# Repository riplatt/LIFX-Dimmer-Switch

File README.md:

# LIFX-Dimmer-Switch
A Dimmer switch for the LIFX lights

Control the LIFX light with a physical dimmer switch

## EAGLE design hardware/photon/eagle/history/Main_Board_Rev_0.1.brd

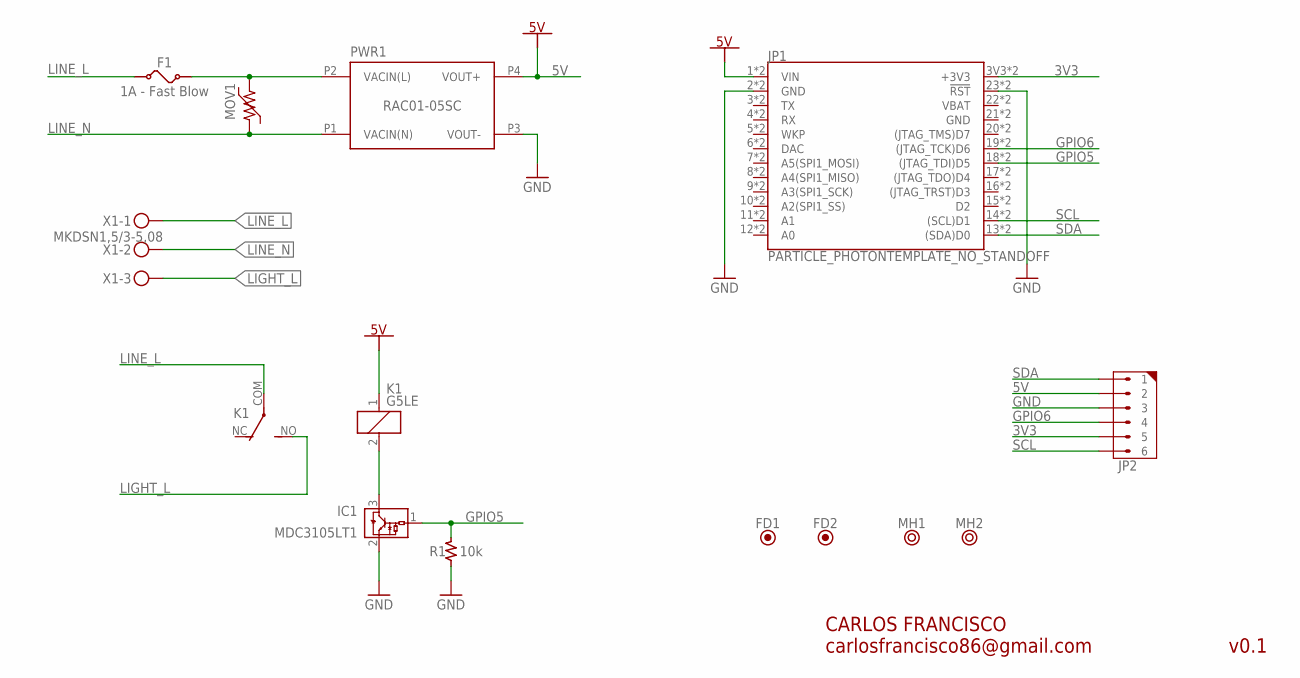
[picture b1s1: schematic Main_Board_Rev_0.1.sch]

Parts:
F1: 1A - Fast Blow; FUSE3.6X10MM
FD1, FD2: FIDUCIALBFID; BOARD_FIDUCIAL
IC1: MDC3105LT1; SOT23
JP1: PARTICLE_PHOTONTEMPLATE_NO_STANDOFF; PARTICLE_PHOTON_TEMPLATE_NO_STANDOFF
JP2: 6X1THT_254MM; HDRV6W63P254_6X1_1520X280H680
K1: G5LE
MH1, MH2: MOUNTING_HOLE3.5MM; MTGP500H350
MOV1: MOV-ROV10H_P; ROV10H_P
PWR1: RAC01-05SC; LOW_PROFILE_POWER_MODULE
R1: 10k; RESC2012X60L35N
X1: MKDSN1,5/3-5,08

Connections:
3V3: JP1.3V3 (+3V3), JP1.24 (+3V3), JP2.5
5V: JP1.1 (VIN), JP1.VIN, JP2.2, K1.1, PWR1.P4 (VOUT+)
GND: IC1.2 (GND), JP1.2 (GND), JP1.21 (GND), JP1.23 (!RST!), JP1.GND@0 (GND), JP1.GND@2 (GND), JP1.RST (!RST!), JP2.3, PWR1.P3 (VOUT-), R1.1
GPIO5: IC1.1 (VIN), JP1.18 ((JTAG_TDI)D5), JP1.D5 ((JTAG_TDI)D5), R1.2
GPIO6: JP1.19 ((JTAG_TCK)D6), JP1.D6 ((JTAG_TCK)D6), JP2.4
LIGHT_L: K1.NO (S), X1.3
LINE_L: F1.P$1, K1.COM, X1.1
LINE_L_F: F1.P$2, MOV1.2, PWR1.P2 (VACIN(L))
LINE_N: MOV1.1, PWR1.P1 (VACIN(N)), X1.2
unnamed: IC1.3 (VOUT), K1.2
SCL: JP1.14 ((SCL)D1), JP1.D1 ((SCL)D1), JP2.6
SDA: JP1.13 ((SDA)D0), JP1.D0 ((SDA)D0), JP2.1
VBAT: JP1.22 (VBAT), JP1.VBAT

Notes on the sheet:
CARLOS FRANCISCO carlosfrancisco86@gmail.com
v0.1

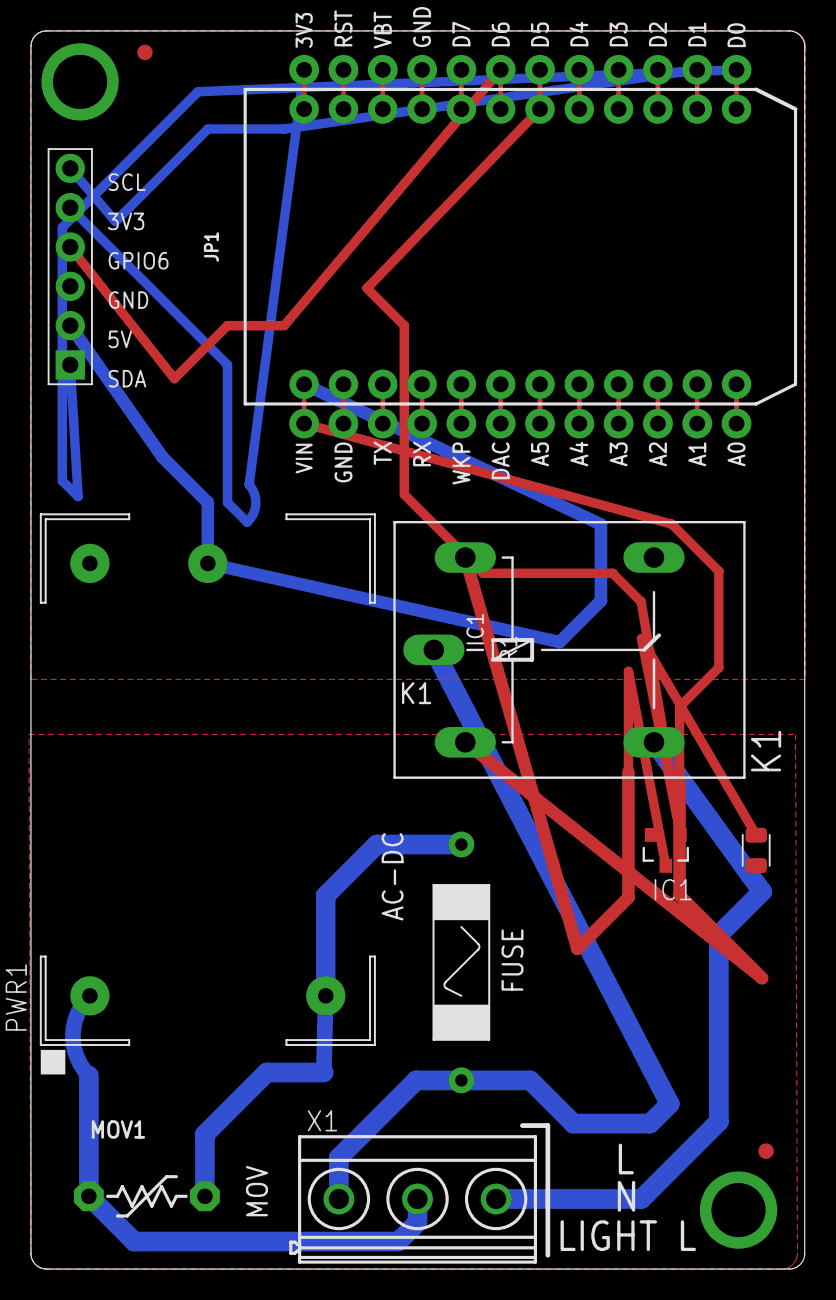
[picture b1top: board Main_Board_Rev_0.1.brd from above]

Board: 2 copper layers, 50.0 x 80.0 mm, 13 parts (0 on the bottom side), 13 nets.

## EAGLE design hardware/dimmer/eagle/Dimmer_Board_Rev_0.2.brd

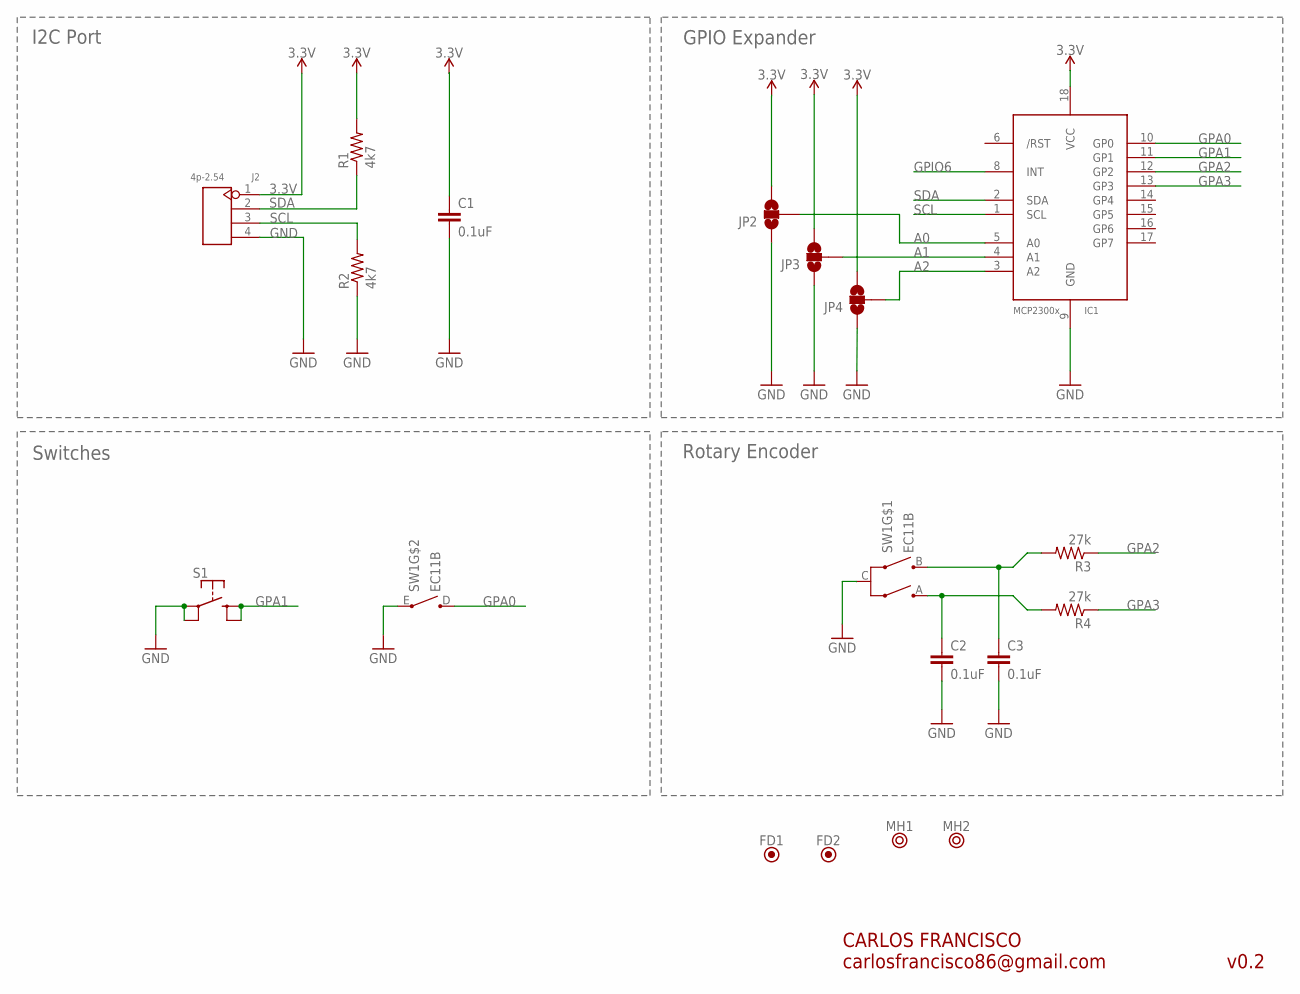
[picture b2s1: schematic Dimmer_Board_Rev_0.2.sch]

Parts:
C1, C2, C3: 0.1uF; C0805
FD1, FD2: FIDUCIALBFID; BOARD_FIDUCIAL
IC1: MCP23008/SO; SO18W
J2: 4p-2.54; H4-2.54
JP2, JP3, JP4: JUMPER-SMT_3_NO_SILK; SMT-JUMPER_3_NO_SILK
MH1, MH2: MOUNTING_HOLE3.5MM; MTGP500H350
R1, R2: 4k7; R0805
R3, R4: 27k; R0805
S1: BUTTON-4KSC; KSC_X
SW1: EC11B; EC11B-V

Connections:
3.3V: C1.1, IC1.18 (VCC), J2.1, JP2.3, JP3.3, JP4.3, R1.2
A: C2.1, R4.2, SW1.A
A0: IC1.5 (A0), JP2.2
A1: IC1.4 (A1), JP3.2
A2: IC1.3 (A2), JP4.2
B: C3.1, R3.2, SW1.B
GND: C1.2, C2.2, C3.2, IC1.9 (GND), J2.4, JP2.1, JP3.1, JP4.1, R2.1, S1.1, S1.2, SW1.C, SW1.E
GPA0: IC1.10 (GP0), SW1.D
GPA1: IC1.11 (GP1), S1.3, S1.4
GPA2: IC1.12 (GP2), R3.1
GPA3: IC1.13 (GP3), R4.1
GPIO6: IC1.8 (INT)
SCL: IC1.1 (SCL), J2.3, R2.2
SDA: IC1.2 (SDA), J2.2, R1.1

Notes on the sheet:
CARLOS FRANCISCO carlosfrancisco86@gmail.com
v0.2
I2C Port
GPIO Expander
Switches
Rotary Encoder

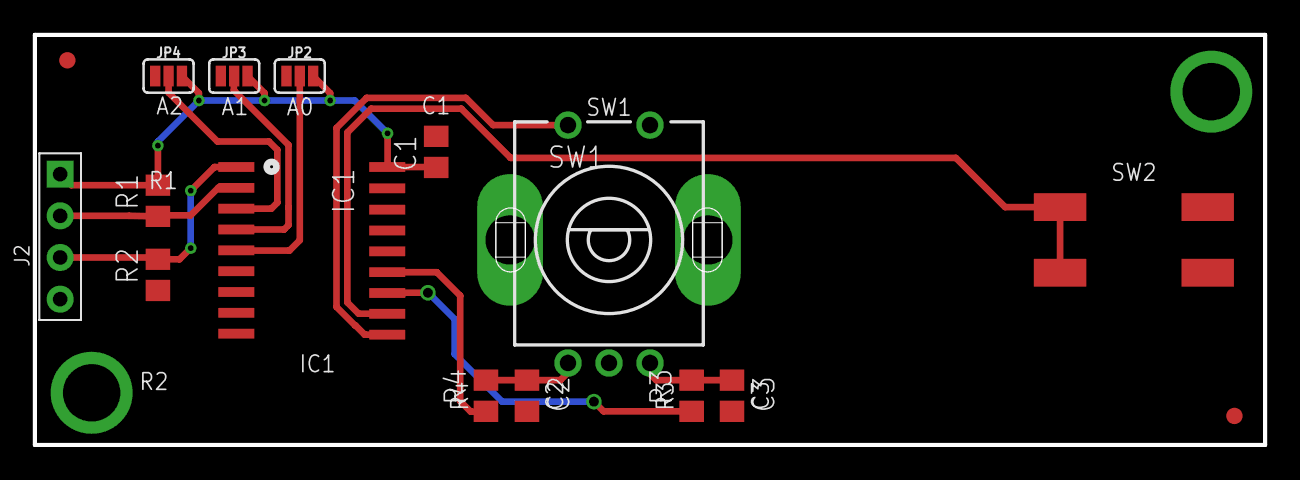
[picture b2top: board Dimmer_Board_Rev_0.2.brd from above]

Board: 2 copper layers, 75.0 x 25.0 mm, 18 parts (0 on the bottom side), 13 nets.

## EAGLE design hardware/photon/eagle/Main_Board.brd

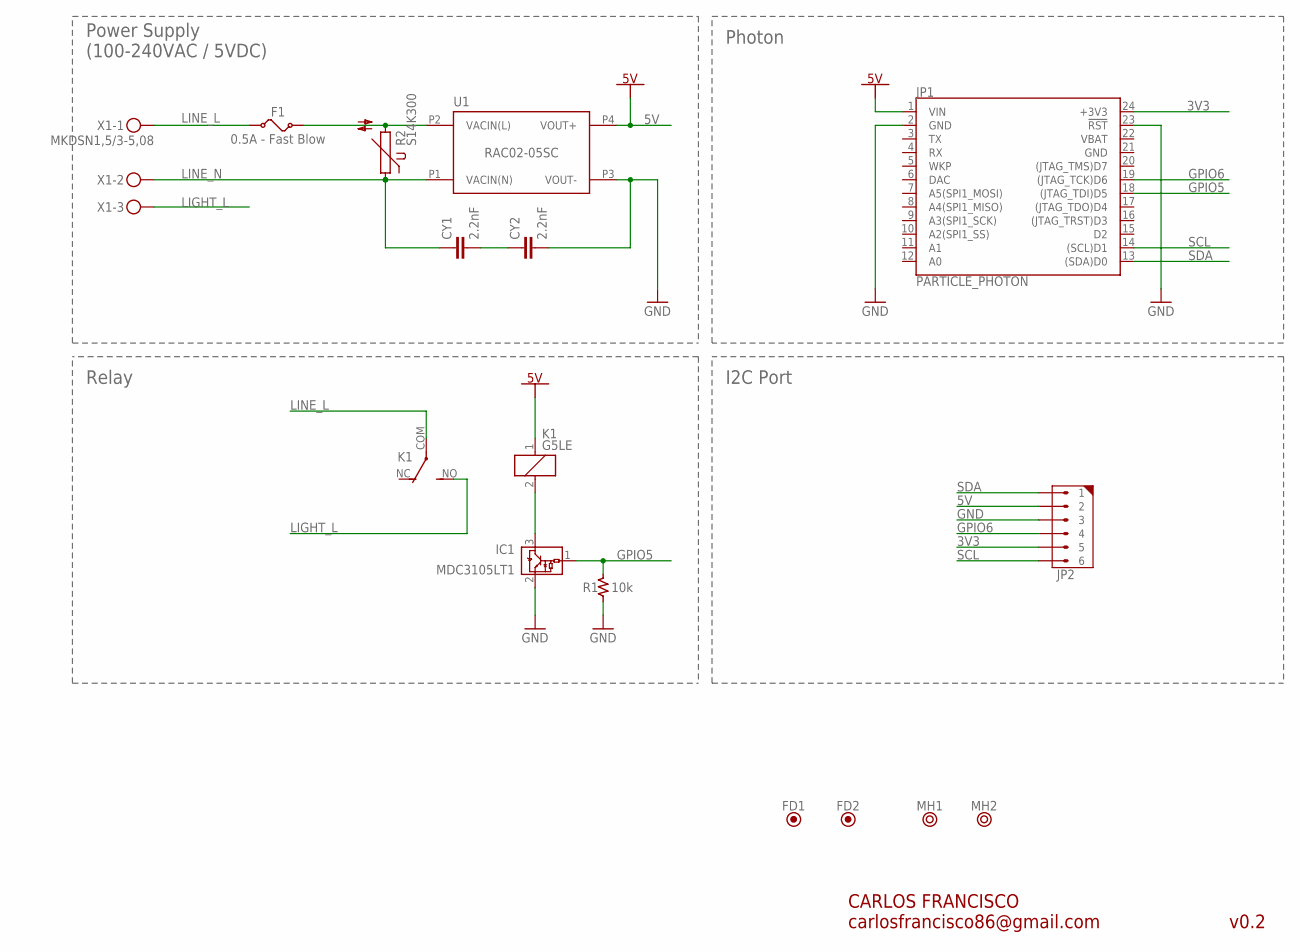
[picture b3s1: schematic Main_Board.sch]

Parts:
CY1, CY2: 2.2nF; 564R30TSD22
F1: 0.5A - Fast Blow; FUSE3.6X10MM
FD1, FD2: FIDUCIALBFID; BOARD_FIDUCIAL
IC1: MDC3105LT1; SOT23
JP1: PARTICLE_PHOTON
JP2: 6X1THT_254MM; HDRV6W63P254_6X1_1520X280H680
K1: G5LE
MH1, MH2: MOUNTING_HOLE3.5MM; MTGP500H350
R1: 10k; RESC2012X60L35N
R2: S14K300
U1: RAC02-05SC; LOW_PROFILE_POWER_MODULE
X1: MKDSN1,5/3-5,08

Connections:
3V3: JP1.24 (+3V3), JP2.5
5V: JP1.1 (VIN), JP2.2, K1.1, U1.P4 (VOUT+)
CY1CY2: CY1.2, CY2.1
GND: CY2.2, IC1.2 (GND), JP1.2 (GND), JP1.21 (GND), JP1.23 (!RST!), JP2.3, R1.1, U1.P3 (VOUT-)
GPIO5: IC1.1 (VIN), JP1.18 ((JTAG_TDI)D5), R1.2
GPIO6: JP1.19 ((JTAG_TCK)D6), JP2.4
LIGHT_L: K1.NO (S), X1.3
LINE_L: F1.P$1, K1.COM, X1.1
LINE_L_F: F1.P$2, R2.2, U1.P2 (VACIN(L))
LINE_N: CY1.1, R2.1, U1.P1 (VACIN(N)), X1.2
RELAY_IN: IC1.3 (VOUT), K1.2
SCL: JP1.14 ((SCL)D1), JP2.6
SDA: JP1.13 ((SDA)D0), JP2.1
VBAT: JP1.22 (VBAT)

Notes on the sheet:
CARLOS FRANCISCO carlosfrancisco86@gmail.com
v0.2
Photon
Power Supply (100-240VAC / 5VDC)
Relay
I2C Port

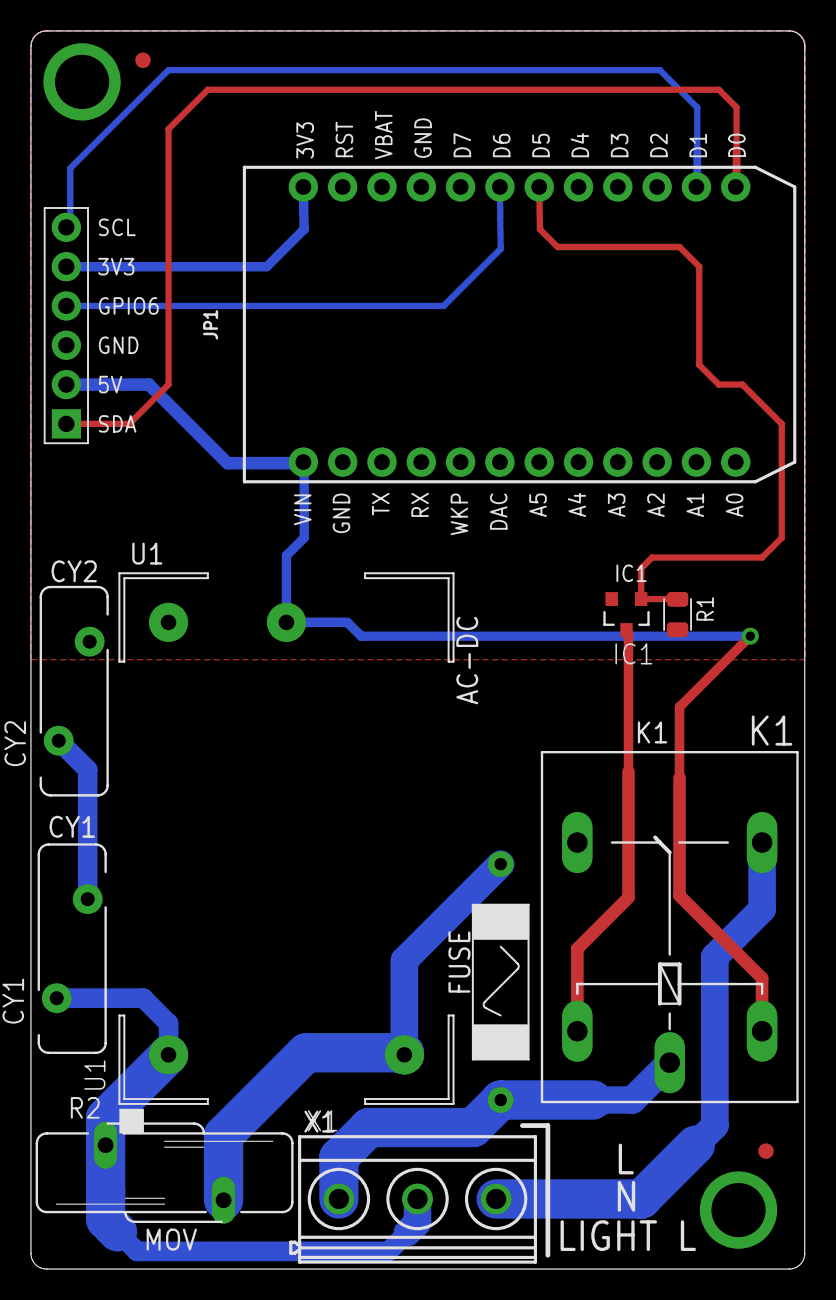
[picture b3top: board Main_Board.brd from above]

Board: 2 copper layers, 50.0 x 80.0 mm, 15 parts (0 on the bottom side), 13 nets.

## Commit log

2016-12-29 :tada: Added .gitattributes & .gitignore files
2016-12-29 Initial Upload
2017-01-03 fixing bugs
2017-10-29 Rename light.h to Frimware/photon/light.h
2017-10-29 Rename light.cpp to Firmware/photon/light.cpp
2017-10-29 Rename lifxUDP.h to Firmware/photon/lifxUDP.h
2017-10-29 Rename lifxUDP.cpp to Firmware/photon/lifxUDP.cpp
2017-10-29 Rename lifx.h to Firmware/photon/lifx.h
2017-10-29 Rename Frimware/photon/light.h to Firmware/photon/light.h
2017-10-29 Rename button.cpp to Firmware/photon/button.cpp
2017-10-29 Rename button.h to Firmware/photon/button.h
2017-10-29 Rename common.h to Firmware/photon/common.h
2017-10-29 Rename device.cpp to Firmware/photon/device.cpp
2017-10-29 Rename lifx.cpp to Firmware/photon/lifx.cpp
2017-10-29 Rename device.h to Firmware/photon/device.h
2017-10-29 Rename lifx-dimmer-switch.ino to Firmware/photon/lifx-dimmer-switch.ino
2017-10-29 Rearrange Project Folder
2017-10-29 Rearrange Project Folders
2017-10-29 Tidy-up
2017-10-29 first prints
2017-11-01 Cleaning up Sch
2017-11-02 Updated UDP to send command directly
2017-11-02 clean up
2017-11-02 Removed fade delays
2017-11-04 Fixing Colour Change

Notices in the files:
parts and their libraries:
SparkFun-Jumpers: Licensing: Creative Commons ShareAlike 4.0 International - https://creativecommons.org/licenses/by-sa/4.0
supressor: Copyright (C) 2009, Bob Starr
